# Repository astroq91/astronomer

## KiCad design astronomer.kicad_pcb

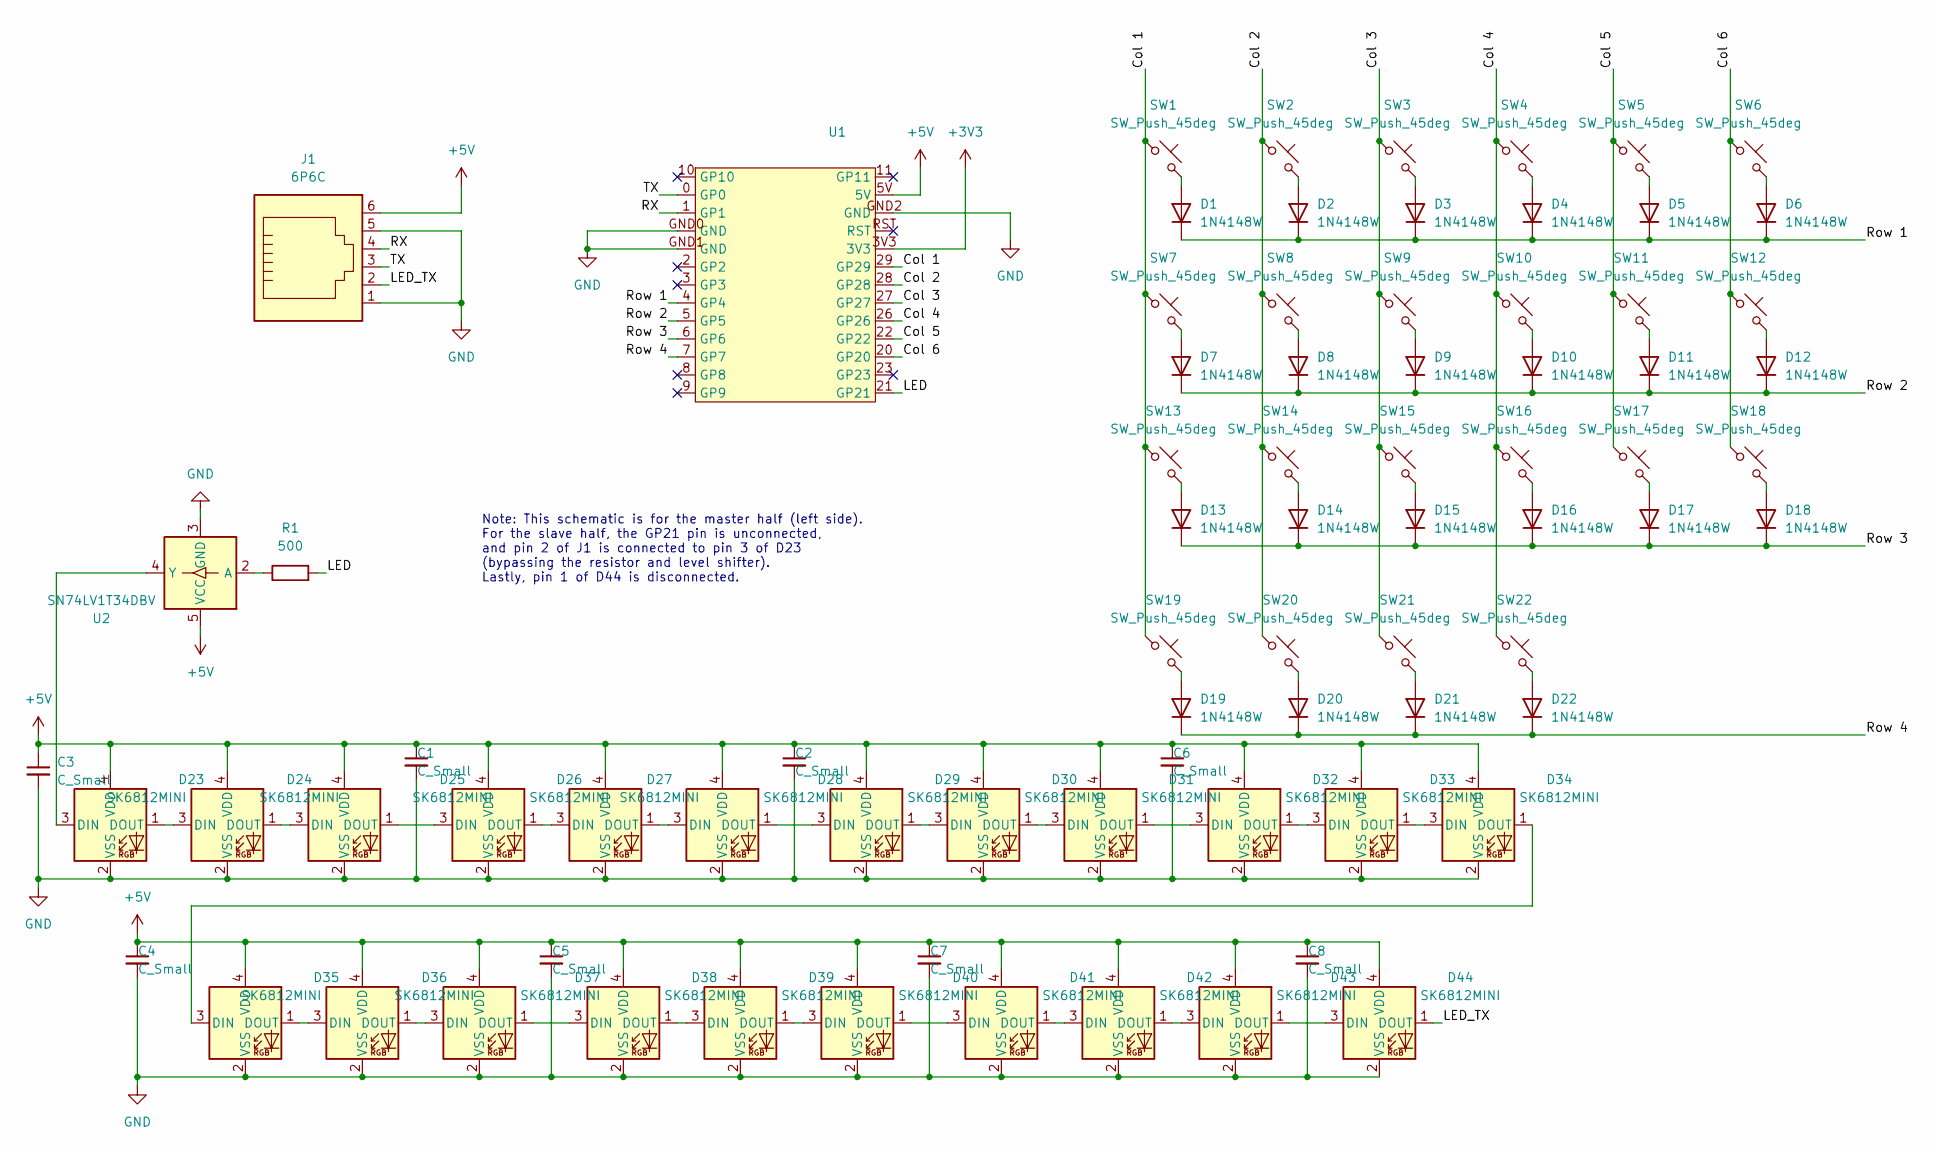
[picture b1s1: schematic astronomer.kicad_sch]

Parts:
C1, C2, C3, C4, C5, C6, C7, C8: C_Small; C_1206_3216Metric
D1, D2, D3, D4, D5, D6, D7, D8, D9, D10, D11, D12, D13, D14, D15, D16, D17, D18, D19, D20, D21, D22: 1N4148W; D_SOD-123 Reversible
D23, D24, D25, D26, D27, D28, D29, D30, D31, D32, D33, D34, D35, D36, D37, D38, D39, D40, D41, D42, D43, D44: SK6812MINI; SK6812-MINI-E
J1: 6P6C; RJ12 6P6C
R1: 500; R_Axial_DIN0207_L6.3mm_D2.5mm_P7.62mm_Horizontal
SW1, SW2, SW3, SW4, SW5, SW6, SW7, SW8, SW9, SW10, SW11, SW12, SW13, SW14, SW15, SW16, SW17, SW18, SW19, SW20, SW21, SW22: SW_Push_45deg; SW_Hotswap_Kailh_Choc_V1_1.00u
U1: RP2040_ProMicro
U2: SN74LV1T34DBV; SOT-23-5

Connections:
+3V3: U1.3V3
+5V: C1.1, C2.1, C3.1, C4.1, C5.1, C6.1, C7.1, C8.1, D23.4 (VDD), D24.4 (VDD), D25.4 (VDD), D26.4 (VDD), D27.4 (VDD), D28.4 (VDD), D29.4 (VDD), D30.4 (VDD), D31.4 (VDD), D32.4 (VDD), D33.4 (VDD), D34.4 (VDD), D35.4 (VDD), D36.4 (VDD), D37.4 (VDD), D38.4 (VDD), D39.4 (VDD), D40.4 (VDD), D41.4 (VDD), D42.4 (VDD), D43.4 (VDD), D44.4 (VDD), J1.6, U1.5V, U2.5 (VCC)
/Col 1: SW1.1, SW7.1, SW13.1, SW19.1, U1.29 (GP29)
/Col 2: SW2.1, SW8.1, SW14.1, SW20.1, U1.28 (GP28)
/Col 3: SW3.1, SW9.1, SW15.1, SW21.1, U1.27 (GP27)
/Col 4: SW4.1, SW10.1, SW16.1, SW22.1, U1.26 (GP26)
/Col 5: SW5.1, SW11.1, SW17.1, U1.22 (GP22)
/Col 6: SW6.1, SW12.1, SW18.1, U1.20 (GP20)
/LED: R1.2, U1.21 (GP21)
/LED_TX: D44.1 (DOUT), J1.2
/RX: J1.4, U1.1 (GP1)
/Row 1: D1.1 (K), D2.1 (K), D3.1 (K), D4.1 (K), D5.1 (K), D6.1 (K), U1.4 (GP4)
/Row 2: D7.1 (K), D8.1 (K), D9.1 (K), D10.1 (K), D11.1 (K), D12.1 (K), U1.5 (GP5)
/Row 3: D13.1 (K), D14.1 (K), D15.1 (K), D16.1 (K), D17.1 (K), D18.1 (K), U1.6 (GP6)
/Row 4: D19.1 (K), D20.1 (K), D21.1 (K), D22.1 (K), U1.7 (GP7)
/TX: J1.3, U1.0 (GP0)
GND: C1.2, C2.2, C3.2, C4.2, C5.2, C6.2, C7.2, C8.2, D23.2 (VSS), D24.2 (VSS), D25.2 (VSS), D26.2 (VSS), D27.2 (VSS), D28.2 (VSS), D29.2 (VSS), D30.2 (VSS), D31.2 (VSS), D32.2 (VSS), D33.2 (VSS), D34.2 (VSS), D35.2 (VSS), D36.2 (VSS), D37.2 (VSS), D38.2 (VSS), D39.2 (VSS), D40.2 (VSS), D41.2 (VSS), D42.2 (VSS), D43.2 (VSS), D44.2 (VSS), J1.1, J1.5, U1.GND0 (GND), U1.GND1 (GND), U1.GND2 (GND), U2.3 (GND)
unnamed: D1.2 (A), SW1.2
unnamed: D2.2 (A), SW2.2
unnamed: D3.2 (A), SW3.2
unnamed: D4.2 (A), SW4.2
unnamed: D5.2 (A), SW5.2
unnamed: D6.2 (A), SW6.2
unnamed: D7.2 (A), SW7.2
unnamed: D8.2 (A), SW8.2
unnamed: D9.2 (A), SW9.2
unnamed: D10.2 (A), SW10.2
unnamed: D11.2 (A), SW11.2
unnamed: D12.2 (A), SW12.2
unnamed: D13.2 (A), SW13.2
unnamed: D14.2 (A), SW14.2
unnamed: D15.2 (A), SW15.2
unnamed: D16.2 (A), SW16.2
unnamed: D17.2 (A), SW17.2
unnamed: D18.2 (A), SW18.2
unnamed: D19.2 (A), SW19.2
unnamed: D20.2 (A), SW20.2
unnamed: D21.2 (A), SW21.2
unnamed: D22.2 (A), SW22.2
unnamed: D23.3 (DIN), U2.4 (Y)
unnamed: D23.1 (DOUT), D24.3 (DIN)
unnamed: D24.1 (DOUT), D25.3 (DIN)
unnamed: D25.1 (DOUT), D26.3 (DIN)
unnamed: D26.1 (DOUT), D27.3 (DIN)
unnamed: D27.1 (DOUT), D28.3 (DIN)
unnamed: D28.1 (DOUT), D29.3 (DIN)
unnamed: D29.1 (DOUT), D30.3 (DIN)
unnamed: D30.1 (DOUT), D31.3 (DIN)
unnamed: D31.1 (DOUT), D32.3 (DIN)
unnamed: D32.1 (DOUT), D33.3 (DIN)
unnamed: D33.1 (DOUT), D34.3 (DIN)
unnamed: D34.1 (DOUT), D35.3 (DIN)
unnamed: D35.1 (DOUT), D36.3 (DIN)
unnamed: D36.1 (DOUT), D37.3 (DIN)
unnamed: D37.1 (DOUT), D38.3 (DIN)
unnamed: D38.1 (DOUT), D39.3 (DIN)
unnamed: D39.1 (DOUT), D40.3 (DIN)
unnamed: D40.1 (DOUT), D41.3 (DIN)
unnamed: D41.1 (DOUT), D42.3 (DIN)
unnamed: D42.1 (DOUT), D43.3 (DIN)
unnamed: D43.1 (DOUT), D44.3 (DIN)
unnamed: R1.1, U2.2 (A)

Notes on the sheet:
Note: This schematic is for the master half (left side). For the slave half, the GP21 pin is unconnected, and pin 2 of J1 is connected to pin 3 of D23 (bypassing the resistor and level shifter). Lastly, pin 1 of D44 is disconnected.

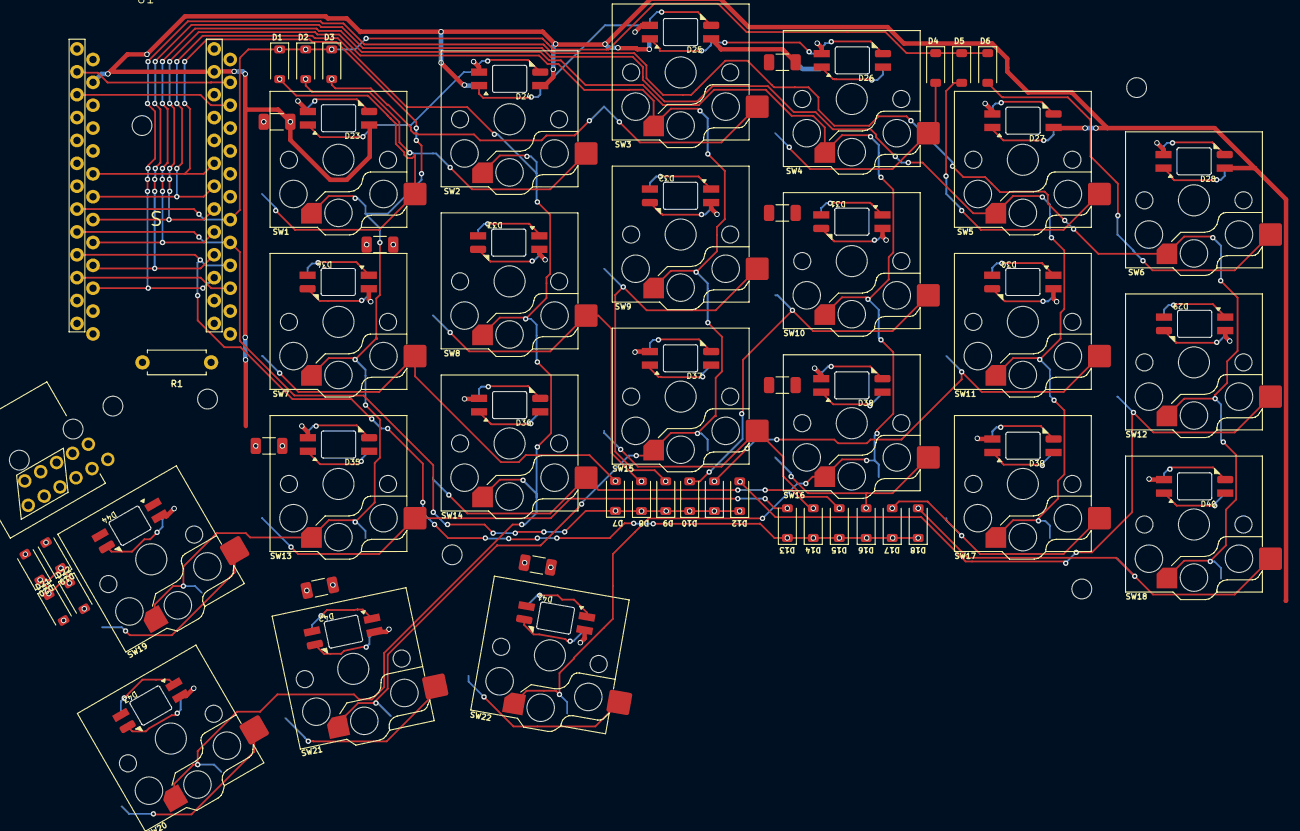
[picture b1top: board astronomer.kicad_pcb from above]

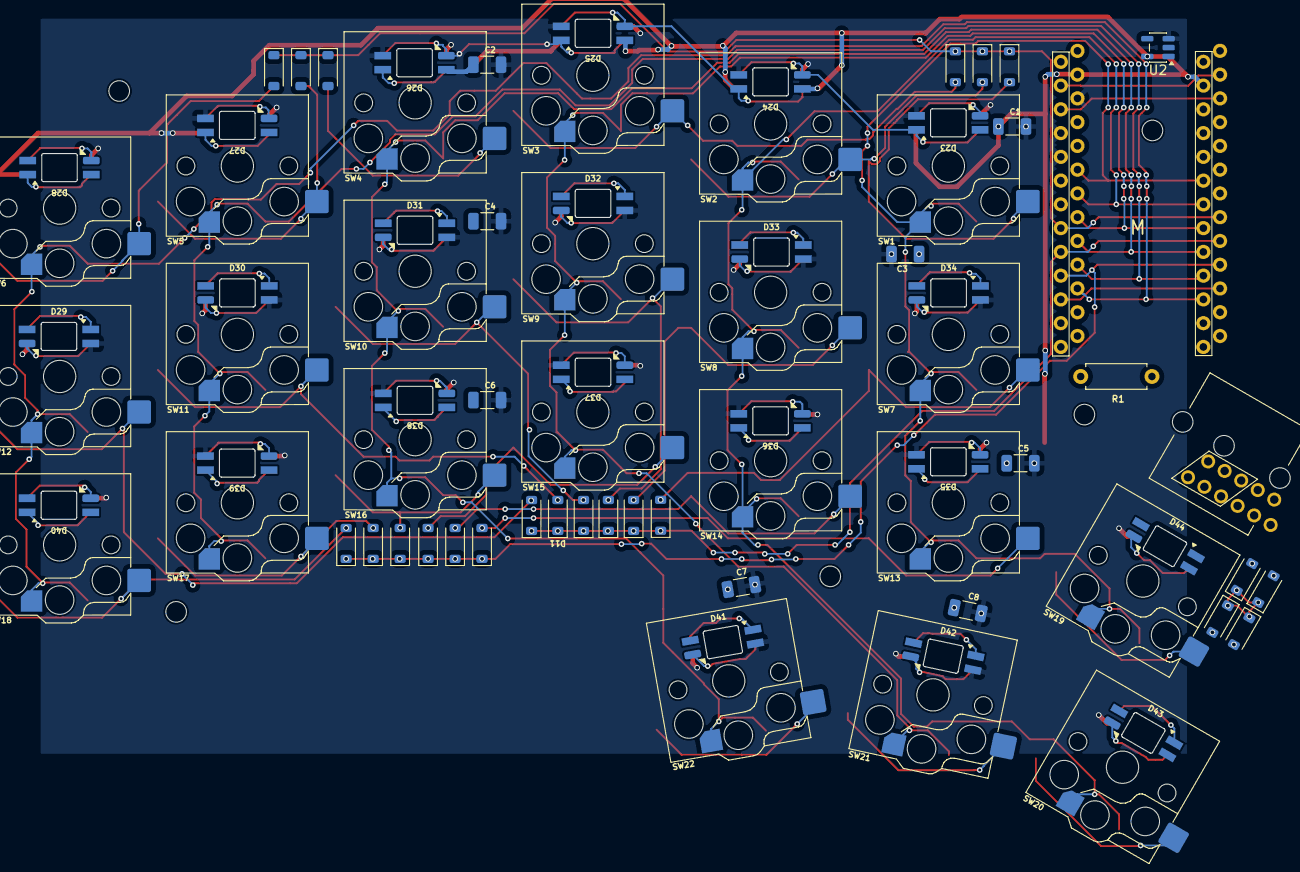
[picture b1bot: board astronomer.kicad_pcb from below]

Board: 2 copper layers, 122.4 x 78.5 mm, 78 parts (32 on the bottom side), 61 nets.

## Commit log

2025-12-10 init
2025-12-10 traces
2025-12-11 lights sch
2025-12-11 pcb lights
2025-12-11 caps
2025-12-11 more traces
2025-12-12 fixed footprints
2025-12-13 revisions
2025-12-15 routes done?
2025-12-15 level shifter
2025-12-18 maybe functional
2025-12-21 minor fixes
2026-01-04 added the footprints + symbols
2026-01-05 Probably works
2026-01-05 Initial routing
2026-01-05 more routing
